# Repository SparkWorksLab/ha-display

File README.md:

<div align="center">

# Home Assistant Display

**A low-power ESPHome e-paper dashboard for Home Assistant.**

A battery-powered Home Assistant display built around an ESP32-S3 and a 4.2" three-color e-paper display.

The device periodically wakes up, connects to Home Assistant, retrieves sensor data, updates the display, and then returns to deep sleep to minimize power consumption.

</div>

---

## Contents

- [Overview](#overview)
- [Features](#features)
- [System Architecture](#system-architecture)
- [Project Structure](#project-structure)
- [Display](#display)
- [Power Management](#power-management)
- [Home Assistant Integration](#home-assistant-integration)
- [Hardware](#hardware)
- [Firmware](#firmware)
- [Enclosure](#enclosure)
- [Installation](#installation)
- [Future Improvements](#future-improvements)
- [Design Principles](#design-principles)
- [References](#references)
- [License](#license)

---

## Overview

The **Home Assistant Display** is a battery-powered e-paper dashboard
designed to provide a quick overview of home information without requiring
a permanently powered screen.

The display combines data from Home Assistant with measurements from local
sensors and presents the information through a modular set of e-paper
widgets.

The low-power architecture allows the device to remain in deep sleep for
most of the time, waking periodically to update the display.

The project is designed to be modular and expandable, with separate
documentation for the firmware, hardware, and enclosure.

---

## Features

* 4.2" three-color e-paper display.
* Home Assistant integration through the ESPHome API.
* Weather forecast display.
* Local temperature, humidity, and atmospheric pressure monitoring.
* BME688 gas resistance and air quality monitoring.
* Smart Plug status monitoring.
* Current and power consumption display.
* Room temperature and humidity monitoring.
* Sensor availability detection.
* Low-power operation using deep sleep.
  * Automatic configurable interval refresh cycle during the day.
  * Extended deep sleep during the night.
* Manual wake-up button.  
* Li-Ion battery voltage monitoring.
* Wi-Fi connection status indication.
* Home Assistant API connection status indication.
* Configurable RGB debug LED.
* Modular display and widget architecture.
* Doxygen documentation.
* *Fail-Safe Operation:* Network mitigation routines preventing infinite loops and battery drain during Wi-Fi or HA outages.

---

## System Architecture

```mermaid
flowchart LR

    HA[Home Assistant]

    subgraph Display["HA Display"]
        ESP[ESP32-S3]
        DISPLAY[4.2-inch E-paper Display]
        BME[BME688]
        BAT[Li-Ion Battery]
        BUTTON[Wake-up Button]
    end

    SENSORS[Room Sensors]
    PLUGS[Smart Plugs]
    WEATHER[Weather Integration]

    SENSORS --> HA
    PLUGS --> HA
    WEATHER --> HA

    HA <-->|ESPHome API / Wi-Fi| ESP

    BME -->|I2C| ESP
    BAT -->|GPIO1| ESP
    BUTTON -->|GPIO4| ESP
    ESP --> DISPLAY
```

The display acts as a low-power endpoint for Home Assistant.

Home Assistant provides aggregated data and configuration, while the ESP32
is responsible for local sensor measurements, display rendering,
connectivity, and power management.

---

## Project Structure

```text
.
├── enclosure/       # 3D-printable enclosure and mechanical documentation
├── firmware/        # ESPHome configuration and C++ firmware
├── hardware/        # Schematics, PCB layouts, and BOMs
├── images/          # Project images and documentation assets
├── README.md        # Main project documentation
└── LICENSE          # AGPL-3.0 License
```

Each major part of the project has its own documentation:

* [Firmware](firmware/) — ESPHome configuration, C++ code,
sensors, display widgets, power management, and Home Assistant
integration.
* [Hardware](hardware/) — electronics, schematics, PCB
revisions, and BOM.
* [Enclosure](enclosure/) — 3D-printable enclosure files,
assembly information, and mechanical details.

---

## Display

The display is divided into several independent widgets.

* **Header**

  * Last update time.
  * Wi-Fi and Home Assistant connection status.
  * Title.
  * Battery status.

* **Top Section**

  * Weather forecast.

* **Middle Section**

  * BME688 environmental and air quality data.
  * Smart Plug monitoring.

* **Bottom Section**

  * Room temperature and humidity sensors.

The display drawing code is organized into reusable functions. This makes it easy to modify the layout or add new widgets without turning the main ESPHome display lambda into a large block of code.

### Display Layout

The 400 × 300 px screen is divided into four sections, each mapped to positions and sizes defined in `layout.h`.

<div align="center">

</div>

---

## Power Management

Low power consumption is one of the main goals of the project.

The device does not remain continuously connected to Wi-Fi. Instead, the ESP32 follows this cycle:

```mermaid
flowchart TD

    A[Wake up] --> B[Connect to Wi-Fi]

    B --> C[Connect to Home Assistant]

    C --> D[Receive Home Assistant data]

    D --> E[Read local sensors]

    E --> F[Update e-paper display]

    F --> G[Wait for display refresh]

    G --> L{Deep sleep enabled?}

    L -->|On| H{Night period?}

    H -->|No| I[Deep sleep for configured interval]

    H -->|Yes| J[Calculate time until wake time]

    J --> K[Extended deep sleep]

    I --> A
    K --> A

    L -->|Off| M[Wait configured interval]
    M --> D

    BUTTON[Manual wake-up button] -. GPIO4 .-> A
```

During the day, the display wakes up and refreshes at the interval configured through Home Assistant.

During the night, it enters a longer deep sleep period and automatically wakes up at the configured morning wake time.

The sleep schedule and daytime sleep duration can be configured directly
from Home Assistant without recompiling or reflashing the firmware.

A physical wake-up button can also be used to wake the device manually.

For detailed implementation information, see
[Power Management](firmware/README.md#power-management) in the firmware
documentation.

---

## Home Assistant Integration

The display communicates with Home Assistant through the ESPHome API.

Home Assistant provides:

* Room sensor data.
* Smart Plug information.
* Weather forecast data.
* Sleep schedule configuration.
* Daytime sleep duration.
* Deep-sleep enable/disable state.

Several Home Assistant helpers are used as persistent configuration
parameters for the display.

The current configuration includes:

* Sleep start hour.
* Wake-up hour.
* Daytime sleep duration.
* Deep-sleep enable/disable.

Because these values are stored by Home Assistant, they remain available while the ESP32 is in deep sleep.

When the display wakes and reconnects to Home Assistant, it retrieves the current configuration and uses it to determine its next operating cycle.

Changes made in Home Assistant therefore take effect on the next wake-up cycle.

The physical wake-up button can be used to apply configuration changes immediately instead of waiting for the next scheduled wake-up.

Detailed Home Assistant configuration is documented in the
[firmware](firmware/README.md#home-assistant-integration) documentation.

---

## Hardware

The HA Display has been developed through two hardware versions:

### Prototype

The prototype is built using an **ESP32-S3-DevKitC-1 development board** and a
2.54mm pitch protoboard. It was used to develop and validate the hardware and
software before designing the dedicated PCB.

Main hardware components:

* ESP32-S3-DevKitC-1 development board.
* WeAct Studio 4.2" (400 × 300 px) three-color e-paper display.
* Bosch BME688 environmental and air quality sensor.
* Li-Ion 18650 battery.
* 1S BMS/protection module.
* TPS63802 buck-boost 3,3v converter module.
* TP4056 USB-C Li-Ion charger module.
* 1 x push button for manual wake-up.

[View prototype hardware documentation](hardware/prototype/README.md)

### v1.0 Dedicated PCB

<div align="center">

</div>

The v1.0 hardware replaces the prototype wiring with a **dedicated 4-layer PCB** designed specifically for the HA Display with controlled USB differential pair impedances and optimized power and ground planes.
* ESP32-S3-DevKitC-1 development board.
* WeAct Studio 4.2" (400 × 300 px) three-color e-paper display.
* Bosch BME680/BME688 environmental sensor.
* Li-Ion 18650 battery.
* BQ24072: Li-Ion battery charger and power-path management IC (prioritizes USB input, bypassing cell micro-cycling).
* TPS63001: High-efficiency buck-boost converter ensuring a stable 3.3V rail down to battery cutoff.
* XB8089D: Integrated SOP8 advanced battery protection sub-circuit.
* Redundant DPDT Switch: Dual parallel-trace slide switch ensuring high mechanical robustness and reduced contact resistance.
* EEPROM: Onboard I2C storage for non-volatile data storage.
* 2 x push buttons for navigation and manual wake-up.
* Test points for debugging and measurements.
* Expansion headers for additional peripherals.
* Jumper at GND to measure current consumption easily.

[View v1.0 hardware documentation](hardware/v1.0/README.md)

### Home Assistant Server

Both versions communicate with a **Home Assistant server running on a
Raspberry Pi 3 B+** through ESPHome.

---

## Firmware

The firmware is based on ESPHome with an additional modular C++ layer for display widgets, battery estimation, power management, layout, and other reusable functionality.

The firmware configuration is divided into small YAML packages, while application-specific functionality is implemented through C++ header files.

This separation makes the firmware easier to maintain and allows hardware configuration, Home Assistant entities, display layout, and application logic to evolve independently.

Go to [firmware](firmware/README.md) documentation.

---

## Enclosure

The project includes a dedicated 3D-printed enclosure designed around the
display and electronics.

The enclosure documentation contains:

* STL files.
* Assembly information.
* Mechanical details.
* Printing recommendations.

Go to [enclosure](enclosure/README.md) documentation.

---

## Installation

The complete installation procedure is documented in the
[firmware](firmware/README.md#installation) documentation.

The general process is:

1. Install Python and ESPHome.
2. Clone this repository.
3. Configure the Home Assistant entities.
4. Configure Wi-Fi credentials.
5. Install the required Home Assistant package.
6. Configure the Home Assistant helpers.
7. Compile the ESPHome firmware.
8. Upload the firmware to the ESP32.

---

## Future Improvements

Some ideas for future development include:

* Particulate matter monitoring.
* Dedicated CO₂ measurement.
* Additional air quality sensors.
* Improved BME688 gas analysis and classification.
* ADC calibration based on measured voltage.
* Battery discharge testing and a custom State of Charge curve.
* Improved State of Charge estimation.
* Dynamic e-paper refresh timing.
* Historical sensor trends.
* Additional Home Assistant entities.
* Configurable display layouts.

---

## Design Principles

The goal of this project is to create a simple, low-power, and fully customizable Home Assistant information display.

The project focuses on:

* Low power consumption.
* Modular code.
* Reusable display widgets.
* Easy integration with Home Assistant.
* Battery operation.
* Simple and accessible hardware.
* Easy future expansion.

The architecture intentionally separates Home Assistant data aggregation from the ESP32 application logic.

Home Assistant provides the information and configuration, while the ESP32 focuses on local sensing, display rendering, connectivity, and power management.

---

## References

* [Home Ambient (Faulty Project).](https://faultyproject.es/category/proyectos/home-ambient/)
* [ESPHome E-ink Weather board.](https://github.com/xangin/eink-weather-board)
* [Material Design Icons Library.](https://pictogrammers.com/library/mdi/)

---

## License

The source code in this repository is licensed under the GNU Affero General Public License v3.0 (AGPL-3.0).

See the [LICENSE](LICENSE) file for the full license text.

Third-party assets included in this repository may be distributed under their respective licenses.

### Third-Party Assets

This project includes the Material Design Icons webfont by Pictogrammers.

The font is distributed under the Apache License 2.0.

See the [Pictogrammers](https://pictogrammers.com/) website and the [Apache License 2.0](https://www.apache.org/licenses/LICENSE-2.0) for more information.

### Images and Photographs

Unless otherwise stated, photographs and images in this repository are copyright © 2026 SparkWorksLab.

They are provided for documentation and demonstration purposes only and are not covered by the AGPL-3.0 License.

Permission is required for their reuse, redistribution, or commercial use.

---

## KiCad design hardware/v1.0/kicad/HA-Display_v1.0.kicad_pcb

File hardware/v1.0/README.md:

<div align="center">

# HA Display: Hardware v1.0

The v1.0 hardware is the first dedicated PCB design for the HA Display,
replacing the prototype assembled on a 2.54mm pitch protoboard.

</div>

---

- [Overview](#overview)
- [Main Features](#main-features)
- [Hardware Specifications](#hardware-specifications)
- [Power Management](#power-management)
- [Pin Assignment](#pin-assignment)
- [PCB Configuration](#pcb-configuration)
- [Schematic](#schematic)
- [PCB Design](#pcb-design)
- [Bill of Materials](#bill-of-materials)
- [Manufacturing Files](#manufacturing-files)
- [Hardware Assembly](#hardware-assembly)
- [Version History](#version-history)

---

## Overview

The dedicated PCB integrates the main hardware required by the HA Display
into a single board, reducing wiring and simplifying assembly.

The board is designed around the ESP32-S3-DevKitC-1 and provides connections
for the e-paper display, BME688 sensor, battery, charger, wake-up button
and other peripherals.

### Top Side

<div align="center">

</div>

### Bottom Side

<div align="center">

</div>

---

## Main Features

* ESP32-S3-DevKitC-1 as main microcontroller.
* Dedicated connection for the 4.2" e-paper display.
* BME688 environmental and air quality sensor interface.
* 1-cell 18650 Li-Ion battery connection.
* Integrated battery voltage measurement.
* BQ24072-based USB-C battery charging and monitoring.
* TPS63001 DC-DC converter to supply 3.3v to the board.
* XB8089D Battery protection IC.
* 2 user buttons capable of wake-up the ESP32.
* Power switch.
* Charging status LEDs.
* EEPROM memory for persistent data storage.
* USB Type-C connector for power and ESP32 USB connectivity.
* Test points for debugging and measurements.
* Expansion headers for additional peripherals.
* Removable GND jumper for easy insertion of an ammeter when measuring
  board current consumption.

---

## Hardware Specifications

<div align="center">

| Parameter | Specification |
|---|---|
| Main MCU | ESP32-S3-DevKitC-1 |
| Display | WeAct Studio 4.2" 400 × 300 px, 3-color e-paper |
| Environmental sensor | Bosch BME688 |
| Battery | 1S 18650 Li-Ion |
| Charger | BQ24072 USB-C |
| Battery protection | XB8089D |
| DC-DC converter | TPS63001 buck-boost |
| EEPROM | M24C64 |
| PCB revision | v1.0 |
| PCB stackup | 4-layer |

</div>

---

## Power Management

The board includes a dedicated power-management chain consisting of:

- **BQ24072** — Li-Ion charging and power-path management.
- **XB8089D** — battery protection.
- **TPS63001** — buck-boost conversion to 3.3 V.
- **Battery voltage divider** — provides battery-voltage monitoring to the ESP32-S3.

---

## Pin Assignment

<div align="center">

| ESP32-S3 GPIO | Function |
|---|---|
| GPIO1 | Battery voltage measurement |
| GPIO8 | I²C SDA |
| GPIO9 | I²C SCL |
| GPIO10 | LCD CS |
| GPIO11 | LCD SDI (MOSI) |
| GPIO12 | LCD SCK |
| GPIO13 | Button 1 |
| GPIO14 | Button 2 |
| GPIO16 | LCD BUSY |
| GPIO17 | LCD RST |
| GPIO18 | LCD D/C |
| GPIO19 | USB D− |
| GPIO20 | USB D+ |
| GPIO48 | DEBUG LED |

</div>

---

## PCB Configuration

This PCB has been designed taking into consideration maximum flexibility.

### Battery Charging Current

Battery charging current can be adjusted with JP1 and JP2 jumpers.

<div align="center">

|JP2 | JP1 | CHARGING CURRENT |
|---|---|---|
| 0  |  0  | 100 mA. USB100 mode |
| 0  |  1  | 500 mA. USB500 mode |
| 1  |  0  | Set by R<sub>ISET<sub> |
| 1  |  1  | Standby (USB suspend mode) |

</div>

By default, R<sub>ISET</sub> is used to set charging current to 890mA: 

$$
R_{\text{ISET}} \, (R_2) = \frac{890 \text{ A}\Omega}{890 \text{ mA}} = 1 \text{ k}\Omega
$$

Current limit is set to 1.3A using R<sub>ILIM</sub>:

$$
R_{\text{ILIM}} \, (R_1) = \frac{1550 \text{ A}\Omega}{1.3 \text{ A}} = 1.2 \text{ k}\Omega
$$

### Charge Termination

The BQ24072 contain a TD input that allows termination to be enabled/ disabled. Connect TD to a logic high to disable charge termination. When termination is disabled, the device goes through the pre-charge, fast-charge and CV phases, then remains in the CV phase. During the CV phase, the charger maintains the output voltage at BAT equal to VBAT(REG), and charging current does not terminate.

This pin can be adjusted using JP3, by default is driven LOW to enable Charge Termination. If Charge Termination needs to be disabled, it can be driven HIGH easily.

### BME68x I²C Address

The BME68x I²C address can be selected using the `J4` solder jumper:

* `0x77` — default configuration.
* `0x76` — when `J4` is soldered to GND.

### MC24xx I²C Address

The MC24xx I²C address can be selected using the `J5` solder jumper:

* `R:0xA1/W:0xA0` — default configuration.
* `R:0xA3/W:0xA2` — when `J5` is soldered to 3.3v.

### Test Points

Three Test Points are provided in the Bottom Layer to enable debugging.

<div align="center">

| TP | Function |
|---|---|
| TP1 | Ground Connection |
| TP2 | Battery Voltage measurement (Vbatt/2) |
| TP3 | 3.3v Supply Voltage |

</div>

### Current Measurement

Current consumption can be measured removing R10 (0Ω) and using J7 to connect an ammeter to the groung return of the circuit. Note that `+` sign is marked on the PCB to ensure right polarity.

This can be very useful to estimate battery life according to the selected refresh interval.

---

## Schematic

The complete schematic is available in both PDF and KiCad formats.

[View the schematic](schematic/HA-Display_v1.0.pdf).

---

## PCB Design

The v1.0 hardware has been developed using a **dedicated 4-layer PCB** designed specifically for the HA Display with controlled USB differential pair impedances and optimized power and ground planes.

The PCB was designed using KiCad. The editable KiCad project files are provided in the `kicad/` directory.

---

## Bill of Materials

The complete Bill of Materials is available in:

* [BOM](manufacturing/HA-Display_v1.0_BOM.csv).

---

## Manufacturing Files

The Gerber and drill files required to manufacture the PCB are available in:

* [Gerber files](manufacturing/HA-Display_v1.0_Gerbers.zip).
* [BOM](manufacturing/HA-Display_v1.0_BOM.csv).
* [Centroid file](manufacturing/HA-Display_v1.0-all-pos.csv).

---

## Hardware Assembly

Refer to Hardware Assembly Guide in the [manufacturing](manufacturing/README.md) folder.

---

## Version History

<div align="center">

| Version | Description |
|---|---|
| v1.0 | First dedicated PCB design |

</div>

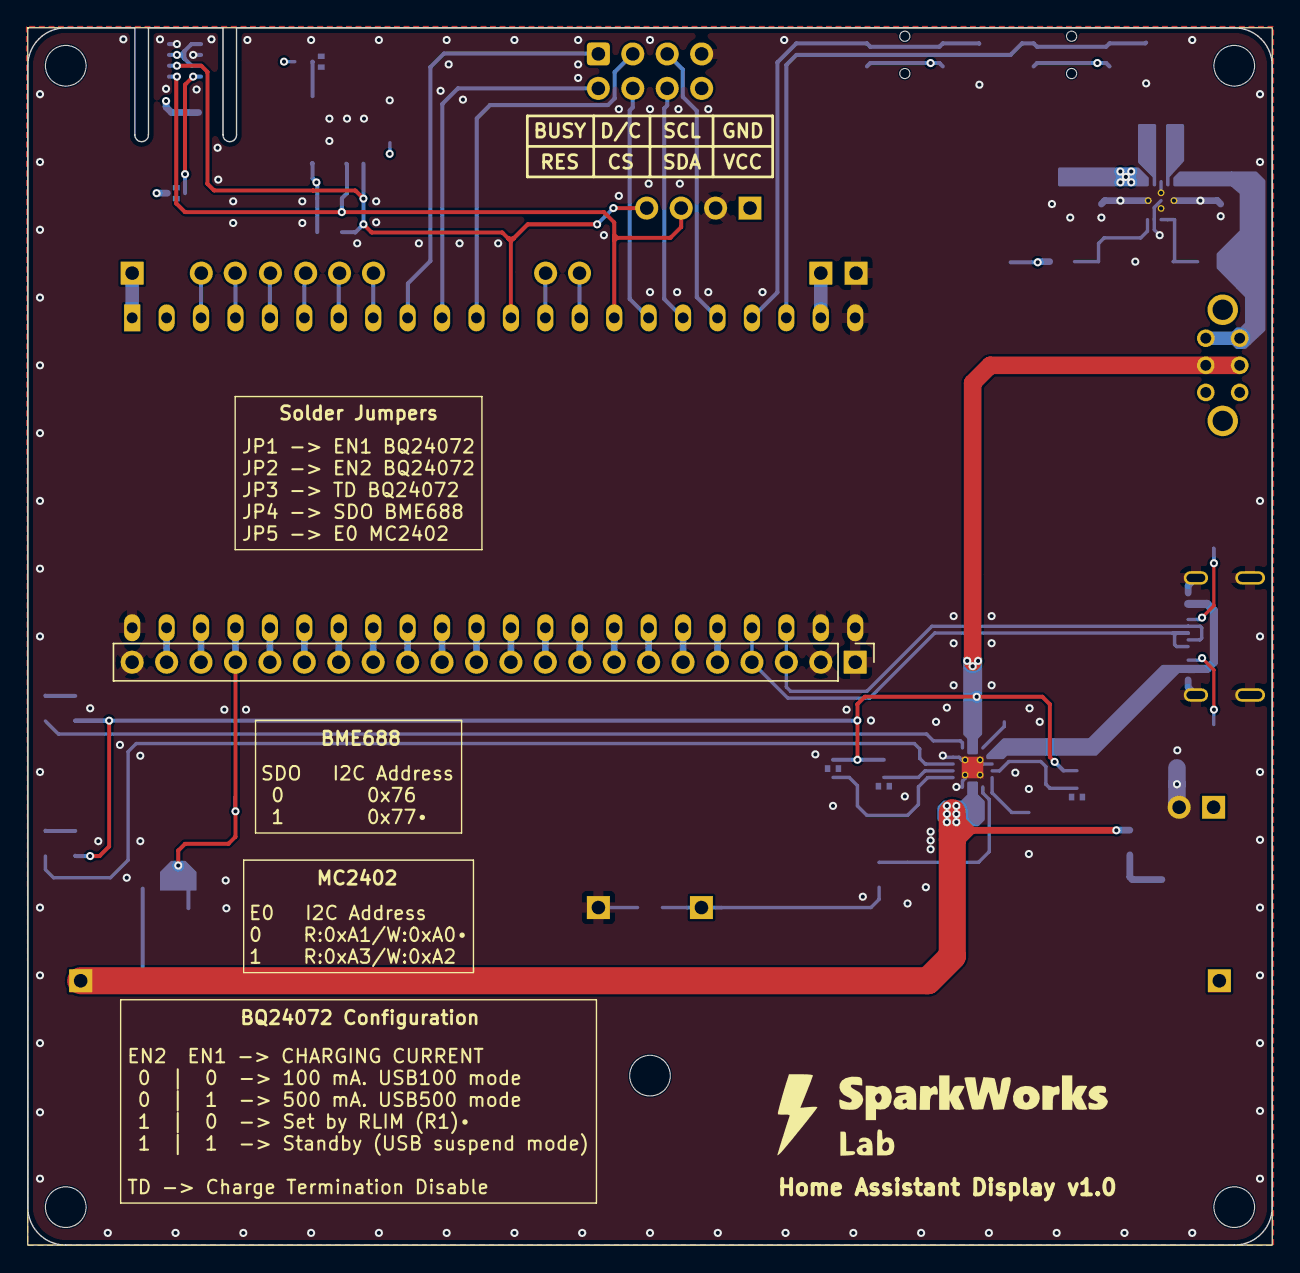
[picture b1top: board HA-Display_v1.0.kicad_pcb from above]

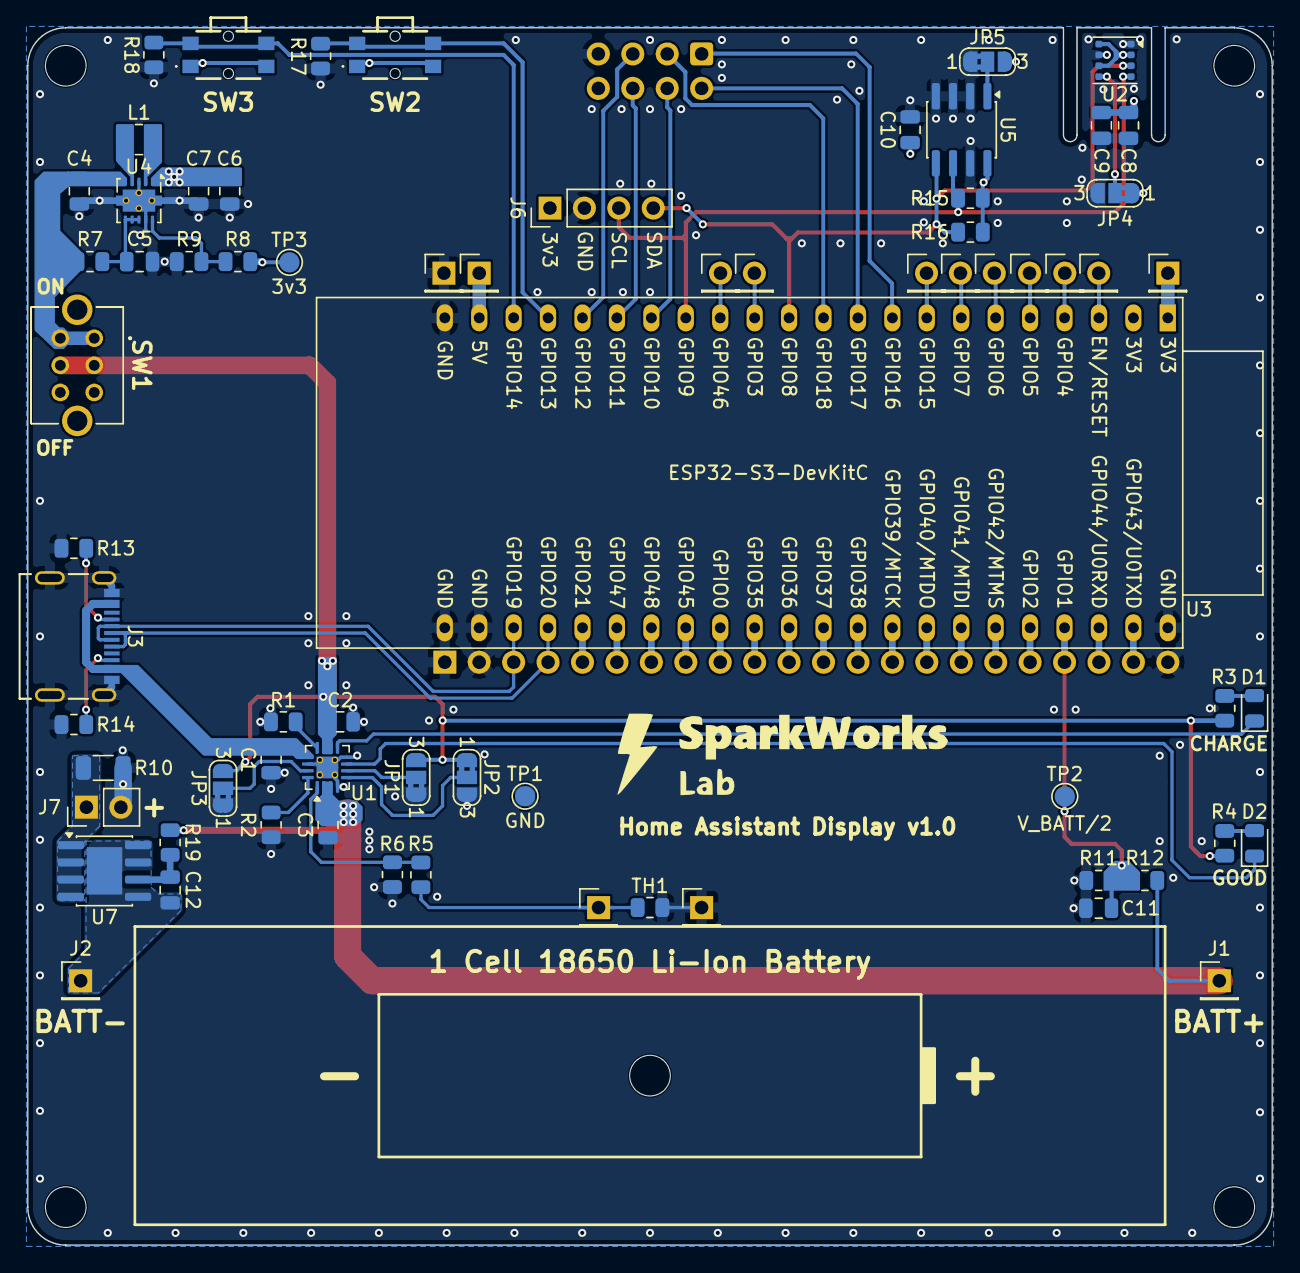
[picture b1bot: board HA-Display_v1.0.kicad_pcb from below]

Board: 4 copper layers, 91.8 x 89.8 mm, 72 parts (70 on the bottom side), 66 nets.

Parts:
3V3, 5V1: B+; PinHeader_1x01_P2.54mm_Vertical
C1: 1u; C_0805_2012Metric
C2, C3: 4.7u; C_0805_2012Metric
C4, C6, C7: 10u; C_0805_2012Metric
C5, C8, C9, C10, C11, C12: 100n; C_0805_2012Metric
D1, D2: LED; LED_0805_2012Metric
GND1: B+; PinHeader_1x01_P2.54mm_Vertical
GPIO3, GPIO4, GPIO5, GPIO6, GPIO7, GPIO15, GPIO46: B+; PinHeader_1x01_P2.54mm_Vertical
J1: B+; PinHeader_1x01_P2.54mm_Vertical
J2: B-; PinHeader_1x01_P2.54mm_Vertical
J3: USB_C_14P; 2171790001_MOL
J4: T+; PinHeader_1x01_P2.54mm_Vertical
J5: T-; PinHeader_1x01_P2.54mm_Vertical
J6: Conn_01x04; PinHeader_1x04_P2.54mm_Vertical
J7: Conn_01x02; PinHeader_1x02_P2.54mm_Vertical
J8: Conn_01x22; PinHeader_1x22_P2.54mm_Vertical
JP1, JP2, JP3, JP4, JP5: Jumper; SolderJumper-3_P1.3mm_Bridged2Bar12_RoundedPad1.0x1.5mm_Num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
L1: 2.2u; L_1008_2520Metric
R1: 1.2K; R_0805_2012Metric
R2, R3, R4, R19: 1K; R_0805_2012Metric
R5: 0; R_0805_2012Metric
R6, R8, R9: NP; R_0805_2012Metric
R7: 100; R_0805_2012Metric
R10: 0; R_1206_3216Metric
R11, R12: 470K; R_0805_2012Metric
R13, R14, R17, R18: 5K1; R_0805_2012Metric
R15, R16: 2K2; R_0805_2012Metric
RST1: B+; PinHeader_1x01_P2.54mm_Vertical
SW1: SW_DPDT_x2; OS202011MA0QN1
SW2, SW3: SW_Push_Dual; 436331045822
TH1: Thermistor_NTC; R_0805_2012Metric
TP1, TP2, TP3: TestPoint; TestPoint_Pad_D1.5mm
U1: BQ24072RGT; VQFN-16-1EP_3x3mm_P0.5mm_EP1.6x1.6mm_ThermalVias
U2: BME688; Bosch_LGA-8_3x3mm_P0.8mm_ClockwisePinNumbering
U3: ESP32-S3-DevKitC
U4: TPS63001; Texas_DRC0010J_ThermalVias
U5: M24C02-WMN; SOIC-8_3.9x4.9mm_P1.27mm
U6: WeAct_4.2_LCD
U7: SOIC-8-1EP_3.9x4.9mm_P1.27mm_EP2.62x3.51mm

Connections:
+3.3V: 3V3.1 (Pin_1_1), C6.1, C7.1, C8.2, C9.1, C10.2, J6.1, JP4.1 (A), JP5.3 (B), R8.2, R15.2, R16.2, SW2.1, SW2.3, SW3.1, SW3.3, TP3.1 (1_1), U2.2 (CSB), U2.6 (VDDIO), U2.8 (VDD), U3.1 (3V3), U3.2 (3V3), U4.1 (VOUT), U5.8 (VCC), U6.8 (VCC)
BATTERY_VOLTAGE: C11.2, J8.19, R11.2, R12.1, TP2.1 (1_1), U3.41 (GPIO1/ADC1_CH0)
BUTTON1: R17.2, SW2.2, SW2.4, U3.19 (GPIO13/ADC2_CH2)
BUTTON2: R18.2, SW3.2, SW3.4, U3.20 (GPIO14/ADC2_CH3)
GND: C1.2, C2.1, C3.2, C4.2, C5.2, C6.2, C7.2, C8.1, C9.2, C10.1, C11.1, GND1.1 (Pin_1_1), J3.A1/B12 (GND), J3.B1/A12 (GND), J3.SH1 (SHIELD), J3.SH2 (SHIELD), J3.SH3 (SHIELD), J3.SH4 (SHIELD), J5.1 (Pin_1_1), J6.2, J7.2, J8.1, J8.2, J8.22, JP1.1 (A), JP2.3 (B), JP3.1 (A), JP4.3 (B), JP5.1 (A), R1.1, R2.1, R6.1, R9.1, R10.1, R11.1, R13.2, R14.2, R17.1, R18.1, TH1.2, TP1.1 (1_1), U1.4 (~CE), U1.8 (VSS), U1.14 (TMR), U1.17 (VSS), U2.1 (GND), U2.7 (GND), U3.22 (GND), U3.23 (GND), U3.24 (GND), U3.44 (GND), U4.3 (PGND), U4.9 (GND), U4.11 (PGND), U5.2 (E1), U5.3 (E2), U5.4 (VSS), U5.7 (~WC), U6.7 (GND)
GPIO0: J8.9, U3.31 (GPIO0)
GPIO2: J8.18, U3.40 (GPIO2/ADC1_CH1)
GPIO21: J8.5, U3.27 (GPIO21)
GPIO35: J8.10, U3.32 (GPIO35)
GPIO36: J8.11, U3.33 (GPIO36)
GPIO37: J8.12, U3.34 (GPIO37)
GPIO38: J8.13, U3.35 (GPIO38)
GPIO39: J8.14, U3.36 (GPIO39/MTCK)
GPIO40: J8.15, U3.37 (GPIO40/MTDO)
GPIO41: J8.16, U3.38 (GPIO41/MTDI)
GPIO42: J8.17, U3.39 (GPIO42/MTMS)
GPIO43: J8.21, U3.43 (GPIO43/U0TXD)
GPIO44: J8.20, U3.42 (GPIO44/U0RXD)
GPIO45: J8.8, U3.30 (GPIO45)
GPIO47: J8.6, U3.28 (GPIO47)
GPIO48: J8.7, U3.29 (GPIO48)
I2C_SCL: J6.3, R15.1, U2.4 (SCK), U3.15 (GPIO9/ADC1_CH8), U5.6 (SCL)
I2C_SDA: J6.4, R16.1, U2.3 (SDI), U3.12 (GPIO8/ADC1_CH7), U5.5 (SDA)
LCD_BUSY: U3.9 (GPIO16/ADC2_CH5/32K_N), U6.1 (BUSY)
LCD_CS: U3.16 (GPIO10/ADC1_CH9), U6.4 (CS)
LCD_D/C: U3.11 (GPIO18/ADC2_CH7), U6.3 (D/C)
LCD_RST: U3.10 (GPIO17/ADC2_CH6), U6.2 (RST)
LCD_SCK: U3.18 (GPIO12/ADC2_CH1), U6.5 (SCL)
LCD_SDI: U3.17 (GPIO11/ADC2_CH0), U6.6 (SDA)
unnamed: 5V1.1 (Pin_1_1), U3.21 (5V)
unnamed: D1.2 (A), R3.1
unnamed: D1.1 (K), U1.9 (~CHG)
unnamed: D2.2 (A), R4.1
unnamed: D2.1 (K), U1.7 (~PGOOD)
unnamed: GPIO3.1 (Pin_1_1), U3.13 (GPIO3/ADC1_CH2)
unnamed: GPIO4.1 (Pin_1_1), U3.4 (GPIO4/ADC1_CH3)
unnamed: GPIO5.1 (Pin_1_1), U3.5 (GPIO5/ADC1_CH4)
unnamed: GPIO6.1 (Pin_1_1), U3.6 (GPIO6/ADC1_CH5)
unnamed: GPIO7.1 (Pin_1_1), U3.7 (GPIO7/ADC1_CH6)
unnamed: GPIO15.1 (Pin_1_1), U3.8 (GPIO15/ADC2_CH4/32K_P)
unnamed: GPIO46.1 (Pin_1_1), U3.14 (GPIO46)
unnamed: C3.1, J1.1 (Pin_1_1), R12.2, R19.2, U1.2 (BAT), U1.3 (BAT)
unnamed: C12.2, J2.1 (Pin_1_1), U7.5 (GND), U7.7 (GND), U7.8 (GND), U7.9 (EPAD)
unnamed: J3.A5 (CC1), R13.1
unnamed: J3.B5 (CC2), R14.1
unnamed: J4.1 (Pin_1_1), R5.2, TH1.1
unnamed: J7.1, R10.2, U7.1 (VM), U7.2 (VM), U7.3 (VM), U7.4 (VM)
unnamed: C2.2, JP1.3 (B), JP2.1 (A), JP3.3 (B), R3.2, R4.2, SW1.2 (B), SW1.5 (B), U1.10 (OUT), U1.11 (OUT)
unnamed: JP1.2 (C), U1.6 (EN1)
unnamed: JP2.2 (C), U1.5 (EN2)
unnamed: JP3.2 (C), U1.15 (TD)
unnamed: JP4.2 (C), U2.5 (SDO)
unnamed: JP5.2 (C), U5.1 (E0)
unnamed: RST1.1 (Pin_1_1), U3.3 (CHIP_PU)
unnamed: R1.2, U1.12 (ILIM)
unnamed: R2.2, U1.16 (ISET)
unnamed: R5.1, R6.2, U1.1 (TS)
unnamed: C5.1, R7.2, U4.6 (EN), U4.7 (PS/SYNC), U4.8 (VINA)
unnamed: R8.1, R9.2, U4.10 (FB)
unnamed: L1.2, U4.4 (L1)
unnamed: L1.1, U4.2 (L2)
unnamed: C12.1, R19.1, U7.6 (VDD)
USB_D+: J3.A6 (D+), J3.B6 (D+), J8.4, U3.26 (GPIO20/USB_D+)
USB_D-: J3.A7 (D-), J3.B7 (D-), J8.3, U3.25 (GPIO19/USB_D-)
VBUS: C1.1, J3.A4/B9 (VBUS), J3.B4/A9 (VBUS), U1.13 (IN)
V_BATT: C4.1, R7.1, SW1.1 (A), SW1.4 (A), U4.5 (VIN)

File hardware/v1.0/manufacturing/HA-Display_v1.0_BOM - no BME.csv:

Comment,Designator,Footprint,LCSC Part Number
1uF,C1,805,C28323
4.7uF,"C2, C3",805,C1779
10uF,"C4, C6, C7",805,C15850
0.1uF,"C5, C8, C9, C10, C11, C12",805,C49678
Red,D1,805,C84256
Green,D2,805,C2297
USB Type C,J3,USB 16P,C3197684
2.2uH,L1,1008,C576403
1K2,R1,805,C17379
1K,"R2, R3, R4, R19",805,C17513
0,R5,805,C17477
100,R7,805,C17408
0,R10,1206,C17888
470K,"R11, R12",805,C17709
5K1,"R13, R14, R17, R18",805,C27834
2K2,"R15, R16",805,C17520
DPDT,SW1,DPDT SW,C221833
10K,TH1,805,C73681
BQ24072RGTR ,U1,QFN-16-EP(3x3),C140288
TPS63001DRCR ,U4,VSON-10-EP(3x3),C28060
M24C64-RMN6TP,U5,SOIC-8,C79988
XB8089D,U7,SOIC-8 EP,C79928

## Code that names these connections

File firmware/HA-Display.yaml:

# =============================================================================
# Home Assistant Display
# =============================================================================
#
# Main ESPHome configuration file.
#
# Includes the project packages, external header files, and hardware-specific
# configuration required to build the Home Assistant Display firmware.

esphome:
  name: ha-display
  includes:
    - include/led.h
    - include/layout.h
    - include/weather_icons.h
    - include/battery.h
    - include/display.h                             # Comment this line to use BSEC2.
    #- include/display_bsec.h                       # Uncomment this line to use BSEC2.
    - include/power.h
  on_boot:
    priority: -100
    then:
      # Refresh Screen
      - script.execute: refresh_display          

# ESP32 DevKit definition.
esp32:
  board: esp32-s3-devkitc-1
  framework:
    type: esp-idf

# YAML files includes.
packages:
  wifi: !include packages/wifi.yaml
  entities: !include packages/entities.yaml
  sensor: !include packages/sensors.yaml            # Comment this line to use BSEC2.
  #sensor: !include packages/sensors_bsec.yaml      # Uncomment this line to use BSEC2.
  font: !include packages/fonts.yaml
  display: !include packages/display.yaml
  forecast: !include packages/forecast.yaml

api:
  reboot_timeout: 0s

# UART Log, change the level if debugging informaiton is needed.
logger:
  level: NONE
  #level: VERY_VERBOSE
  hardware_uart: UART0

# Deep Sleep.
deep_sleep:
  id: deep_sleep_control
  #run_duration: 75s
  sleep_duration: 15min
  
  esp32_ext1_wakeup:
    pins:
      - number: GPIO4       # Prototype PCB.
      #- number: GPIO13     # v1.0 Hardware.
    mode: ANY_HIGH

# Time entity. 
time:
  - platform: homeassistant
    id: ha_time

# Debug LED.
light:
  - platform: esp32_rmt_led_strip
    id: status_led

    pin: GPIO48

    chipset: WS2812
    rgb_order: GRB

    num_leds: 1

    default_transition_length: 0s
    restore_mode: ALWAYS_OFF

# BME68x I2C bus.
i2c:
  sda: GPIO8
  scl: GPIO9
  frequency: 400kHz
  scan: true
  id: i2c_a

# Display SPI.
spi:
  clk_pin: GPIO12
  mosi_pin: GPIO11 

# Global variables.
globals:
  - id: wifi_ok
    type: bool
    restore_value: no
    initial_value: 'false'

  - id: ha_ok
    type: bool
    restore_value: no
    initial_value: 'false'

  - id: sleep_time
    type: int 
    restore_value: no
    initial_value: '0'

  - id: display_update_counter
    type: int
    restore_value: no
    initial_value: '0'

# Timer to update screen when Deep Sleep is OFF.
interval:
  - interval: 1min
    then:
      - if:
          condition:
            binary_sensor.is_off: ha_display_deep_sleep
          then:
            # Increase counter.
            - lambda: |-
                id(display_update_counter)++;

            - if:
                condition:
                  # Check counter and sleep duration.
                  lambda: |-
                    const float sleep_duration = id(ha_sleep_duration).state;
                    return !isnan(sleep_duration) &&
                           sleep_duration > 0 &&
                           id(display_update_counter) >= (int) sleep_duration;
                then:
                  # Update screen if the configured interval has elapsed.
                  - lambda: |-
                      id(display_update_counter) = 0;
                  - script.execute: refresh_display       

# Refresh Screen Script.
script:
  - id: refresh_display
    mode: single
    then:
      - lambda: |-
          ledBoot();

      # Wait 20s for WiFi connection.
      - wait_until:
          condition:
            lambda: |-
              return id(wifi_ok);
          timeout: 20s

      # Wait 15s for HA connection.
      - if:
          condition:
            lambda: |-
              return id(wifi_ok);
          then:
            - wait_until:
                condition:
                  lambda: |-
                    return id(ha_ok);
                timeout: 15s
      
      - lambda: |-
          ledRefresh();

      # Wait 2s to ensure HA data updated.
      - delay: 2s

      # Calculate next Sleep period duration.
      - lambda: |-          
          id(sleep_time) = getSleepDuration(
              (int) id(ha_sleep_start_hour).state,
              (int) id(ha_wake_hour).state);

      # Update display with new retrieved data.
      - component.update: eink
      
      # Delay to ensure full screen refresh.
      - delay: 22s

      - light.turn_off:
          id: status_led

      - delay: 2s

      - if:
          condition:
            or:
              # Enter deep sleep if HA Toggle is ON.
              - binary_sensor.is_on: ha_display_deep_sleep

              # Enter deep sleep if WiFi not connected.
              - not:
                  lambda: |-
                    return id(wifi_ok);
                  
              # Enter deep sleep if Home Assistant not connected.
              - not:
                  lambda: |-
                    return id(ha_ok);
          then:
            - deep_sleep.enter:
                id: deep_sleep_control
                sleep_duration: !lambda |-
                  return id(sleep_time);

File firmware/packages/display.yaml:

# =============================================================================
# Display Configuration
# =============================================================================
#
# Configures the e-paper display and the main display update lambda.
#
# The display layout is implemented through reusable drawing functions defined
# in the project header files.

display:
  - platform: epaper_spi
    id: eink
    model: WeAct-4.2in-3c
    dimensions:
      width: 400
      height: 300
    cs_pin: GPIO10            
    busy_pin: GPIO18          # Prototype PCB.
    dc_pin: GPIO17            # Prototype PCB.
    reset_pin: GPIO16         # Prototype PCB.
    #busy_pin: GPIO16         # v1.0 Hardware.
    #dc_pin: GPIO18           # v1.0 Hardware.
    #reset_pin: GPIO17        # v1.0 Hardware.

    reset_duration: 2ms
    update_interval: never
    full_update_every: 1
    data_rate: 10MHz

    lambda: |-

      drawFrame(it);

      drawHeader(it);

      drawForecast(it);

      drawAirSensor(it);

      drawSmartPlugs(it);

      drawRoomSensors(it);
      
